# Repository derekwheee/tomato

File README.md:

# tomato

A hardware pomodoro timer

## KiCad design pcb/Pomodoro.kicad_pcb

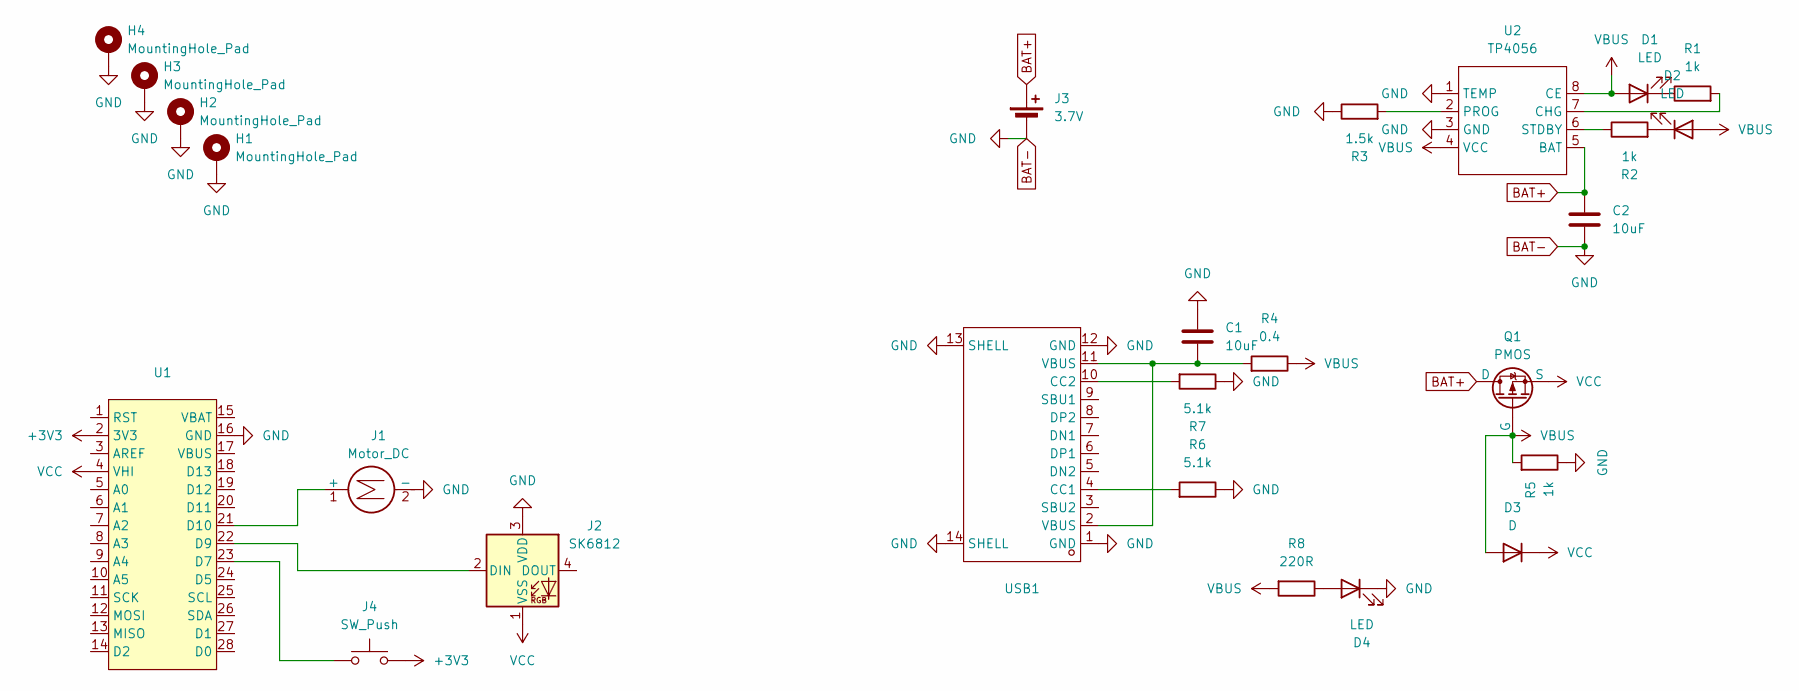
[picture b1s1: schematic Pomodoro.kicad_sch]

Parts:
C1, C2: 10uF; C_0603_1608Metric; LCSC Part # C19702
D1: LED; LED_1206_3216Metric; LCSC Part # C965827
D2, D4: LED; LED_1206_3216Metric; LCSC Part # C965822
D3: D; D_SMA; LCSC Part # C2480
H1, H2, H3, H4: MountingHole_Pad; MountingHole_2.2mm_M2_Pad
J1: Motor_DC; JST_PH_B2B-PH-K_1x02_P2.00mm_Vertical; LCSC Part # C131337
J2: SK6812; JST_PH_B3B-PH-K_1x03_P2.00mm_Vertical; LCSC Part # C131339
J3: 3.7V; JST_PH_B2B-PH-K_1x02_P2.00mm_Vertical; LCSC Part # C131337
J4: SW_Push; SW_SPST_Omron_B3F-40xx
Q1: PMOS; SOT-23-3; LCSC Part # C9900157587
R1, R2, R5: 1k; R_1206_3216Metric; LCSC Part # C1469
R3: 1.5k; R_1206_3216Metric; LCSC Part # C1471
R4: 0.4; R_1206_3216Metric; LCSC Part # C2934306
R6, R7: 5.1k; R_1206_3216Metric; LCSC Part # C2907509
R8: 220R; R_1206_3216Metric; LCSC Part # C25363
U1: ItsyBitsy_M4_V2
U2: TP4056; SOP-8_3.9x4.9mm_P1.27mm; LCSC Part # C382139
USB1: USB-C-SMD_TYPE-C-6PIN-2MD-073; Manufacturer Part TYPE-C 16PIN 2MD(073); LCSC Part # C2765186

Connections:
+3V3: J4.2, U1.2 (3V3)
BAT+: C2.1, J3.1 (+), Q1.3 (D), U2.5 (BAT)
BAT-: C1.1, C2.2, D4.1 (K), H1.1, H2.1, H3.1, H4.1, J1.2 (-), J2.3 (VDD), J3.2 (-), R3.1, R5.1, R6.1, R7.1, U1.16 (GND), U2.1 (TEMP), U2.3 (GND), USB1.1 (GND), USB1.12 (GND), USB1.13 (SHELL), USB1.14 (SHELL)
unnamed: C1.2, R4.2, USB1.2 (VBUS), USB1.11 (VBUS)
unnamed: D1.1 (K), R1.1
unnamed: D2.1 (K), R2.2
unnamed: D4.2 (A), R8.1
unnamed: J1.1 (+), U1.21 (D10)
unnamed: J2.2 (DIN), U1.22 (D9)
unnamed: J4.1, U1.23 (D7)
unnamed: R1.2, U2.7 (CHG)
unnamed: R3.2, U2.2 (PROG)
unnamed: R2.1, U2.6 (STDBY)
unnamed: R6.2, USB1.4 (CC1)
unnamed: R7.2, USB1.10 (CC2)
VBUS: D1.2 (A), D2.2 (A), D3.2 (A), Q1.1 (G), R4.1, R5.2, R8.2, U2.4 (VCC), U2.8 (CE)
VCC: D3.1 (K), J2.1 (VSS), Q1.2 (S), U1.4 (VHI)

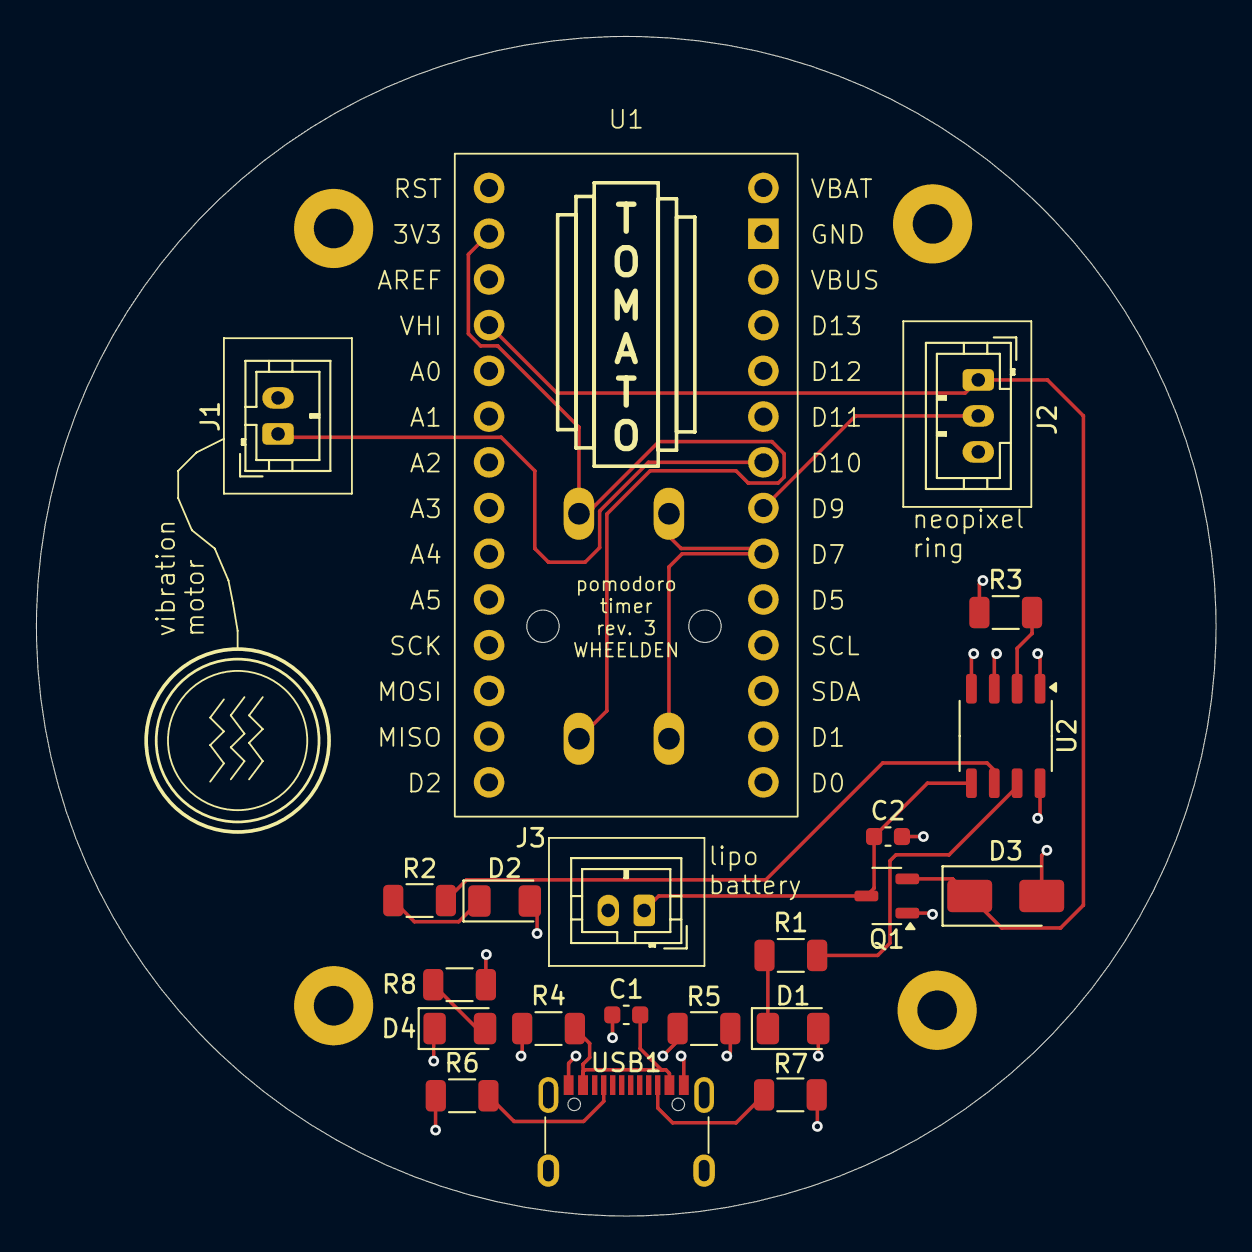
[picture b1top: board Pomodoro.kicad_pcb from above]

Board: 4 copper layers, 65.5 x 65.5 mm, 26 parts (1 on the bottom side), 17 nets.

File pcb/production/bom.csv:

Designator,Footprint,Quantity,Value,LCSC Part #
"C1, C2",0603,2,10uF,C19702
D1,1206,1,LED,C965827 
"D2, D4",1206,2,LED,C965822
D3,D_SMA,1,D,C2480
J1,JST_PH_B2B-PH-K_1x02_P2.00mm_Vertical,1,Motor_DC,C131337 
J2,JST_PH_B3B-PH-K_1x03_P2.00mm_Vertical,1,SK6812,C131339
J3,JST_PH_B2B-PH-K_1x02_P2.00mm_Vertical,1,3.7V,C131337 
J4,SW_SPST_Omron_B3F-40xx,1,SW_Push,
Q1,SOT-23-3,1,PMOS,C9900157587
"R1, R2, R5",1206,3,1k,C1469
R3,1206,1,1.5k,C1471
R4,1206,1,0.4,C2934306
"R6, R7",1206,2,5.1k,C2907509
R8,1206,1,220R,C25363
U1,ItsyBitsy_M4_V2,1,~,
U2,SOP-8_3.9x4.9mm_P1.27mm,1,TP4056,C382139
USB1,USB-C-SMD_TYPE-C-6PIN-2MD-073,1,~,C2765186

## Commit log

2025-01-12 Configure neopixel ring
2025-01-13 Implement timers and animations
2025-01-13 Implement sleep and pause modes
2025-01-14 Fix advance logic, add breath animation
2025-01-16 Add vibration motor
2025-01-20 change todo
2025-01-20 Add README
2025-03-14 Add production files
